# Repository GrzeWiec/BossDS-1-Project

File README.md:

# BossDS-1-Project

My first steps in the world of analog electronics:
- learning the principle of operation of basic electronic components,
- creating the first schematic and PCB in KiCad,
- work based on the famous Boss DS-1 guitar effect,
- getting basic knowledge about the approach to working with an audio signal in electronics.

I created the effect diagram based on the diagram found on the website: https://www.electrosmash.com/boss-ds1-analysis.

All rights to footprints, names, models or symbols belong to their original creators (Boss, SparkFun, M.B.I.)

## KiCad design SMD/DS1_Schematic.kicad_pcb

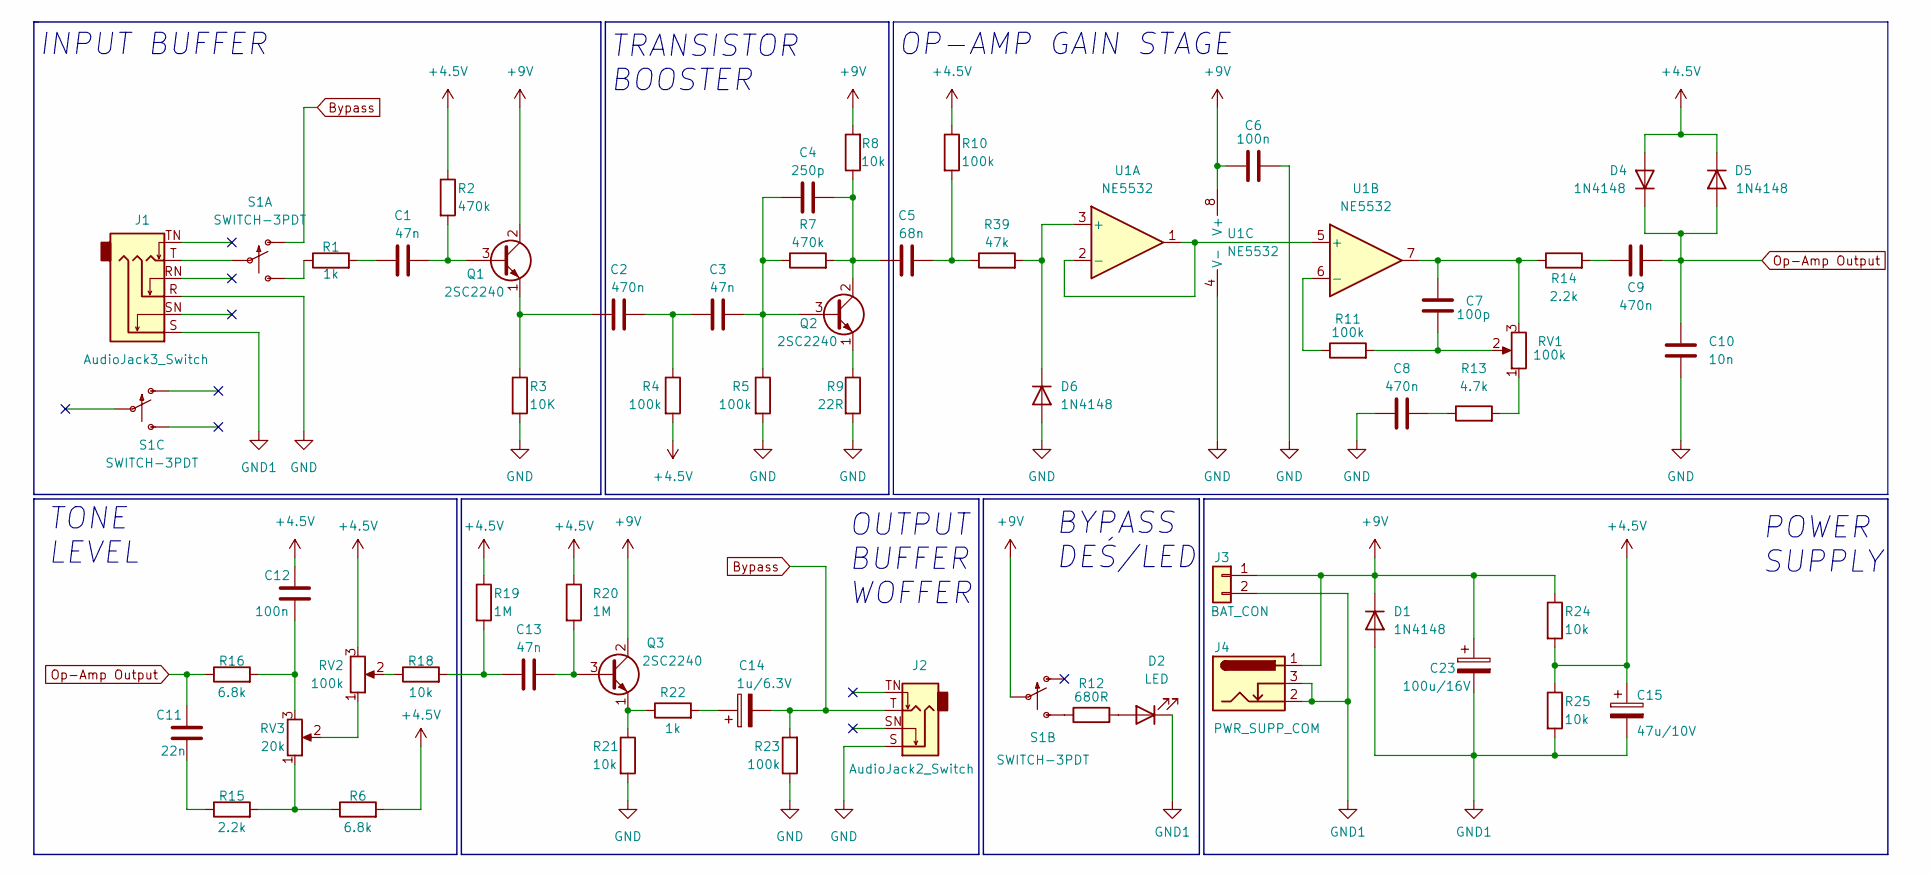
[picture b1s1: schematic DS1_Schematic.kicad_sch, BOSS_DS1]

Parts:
C1, C3, C13: 47n; C_1206_3216Metric_Pad1.33x1.80mm_HandSolder
C2, C8, C9: 470n; C_1206_3216Metric_Pad1.33x1.80mm_HandSolder
C4: 250p; C_1206_3216Metric_Pad1.33x1.80mm_HandSolder
C5: 68n; C_1206_3216Metric_Pad1.33x1.80mm_HandSolder
C6, C12: 100n; C_1206_3216Metric_Pad1.33x1.80mm_HandSolder
C7: 100p; C_1206_3216Metric_Pad1.33x1.80mm_HandSolder
C10: 10n; C_1206_3216Metric_Pad1.33x1.80mm_HandSolder
C11: 22n; C_1206_3216Metric_Pad1.33x1.80mm_HandSolder
C14: 1u/6.3V; C_Elec_4x5.4
C15: 47u/10V; C_1206_3216Metric_Pad1.33x1.80mm_HandSolder
C23: 100u/16V; C_Elec_5x5.8
D1, D4, D5, D6: 1N4148; D_1206_3216Metric_Pad1.42x1.75mm_HandSolder
D2: LED; LED_1206_3216Metric_Pad1.42x1.75mm_HandSolder
J1: AudioJack3_Switch; Jack_6.35mm_Neutrik_NMJ6HFD2_Horizontal
J2: AudioJack2_Switch; Jack_6.35mm_Neutrik_NMJ4HFD2_Horizontal
J3: BAT_CON; PinHeader_1x02_P2.54mm_Vertical
J4: PWR_SUPP_COM; BarrelJack_Wuerth_6941xx301002
Q1, Q2, Q3: 2SC2240; TO-92L_Inline
R1, R22: 1k; R_1206_3216Metric_Pad1.30x1.75mm_HandSolder
R2, R7: 470k; R_1206_3216Metric_Pad1.30x1.75mm_HandSolder
R3: 10K; R_1206_3216Metric_Pad1.30x1.75mm_HandSolder
R4, R5, R10, R11, R23: 100k; R_1206_3216Metric_Pad1.30x1.75mm_HandSolder
R6, R16: 6.8k; R_1206_3216Metric_Pad1.30x1.75mm_HandSolder
R8, R18, R21, R24, R25: 10k; R_1206_3216Metric_Pad1.30x1.75mm_HandSolder
R9: 22R; R_1206_3216Metric_Pad1.30x1.75mm_HandSolder
R12: 680R; R_1206_3216Metric_Pad1.30x1.75mm_HandSolder
R13: 4.7k; R_1206_3216Metric_Pad1.30x1.75mm_HandSolder
R14, R15: 2.2k; R_1206_3216Metric_Pad1.30x1.75mm_HandSolder
R19, R20: 1M; R_1206_3216Metric_Pad1.30x1.75mm_HandSolder
R39: 47k; R_1206_3216Metric_Pad1.30x1.75mm_HandSolder
RV1, RV2: 100k; PinHeader_1x03_P2.54mm_Vertical
RV3: 20k; PinHeader_1x03_P2.54mm_Vertical
S1: SWITCH-3PDT; STOMP-SWITCH-3PDT
U1: NE5532; DIP-8_W7.62mm_LongPads

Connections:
+4.5V: C12.1, C15.1, D4.2 (A), D5.1 (K), R2.1, R4.2, R6.2, R10.1, R19.1, R20.1, R24.2, R25.1, RV2.3
+9V: C6.1, C23.1, D1.1 (K), J3.1, J4.1, Q1.2 (C), Q3.2 (C), R8.2, R24.1, S1.P$5, U1.8 (V+)
Bypass: C14.2, J2.T, R23.2, S1.P$1 (O)
GND: C6.2, C8.1, C10.2, D6.2 (A), J1.R, J2.S, R3.2, R5.2, R9.2, R21.2, R23.1, U1.4 (V-)
GND1: C15.2, C23.2, D1.2 (A), D2.1 (K), J1.S, J3.2, J4.2, J4.3, R25.2
unnamed: C1.1, R1.2
unnamed: C1.2, Q1.3 (B), R2.2
unnamed: C2.1, Q1.1 (E), R3.1
unnamed: C2.2, C3.2, R4.1
unnamed: C3.1, C4.1, Q2.3 (B), R5.1, R7.1
unnamed: C4.2, C5.2, Q2.2 (C), R7.2, R8.1
unnamed: C5.1, R10.2, R39.1
unnamed: C7.1, R14.1, RV1.3, U1.7
unnamed: C7.2, R11.2, RV1.2
unnamed: C8.2, R13.1
unnamed: C9.1, R14.2
unnamed: C11.2, R15.1
unnamed: C12.2, R16.2, RV3.3
unnamed: C13.1, Q3.3 (B), R20.2
unnamed: C13.2, R18.2, R19.2
unnamed: C14.1, R22.2
unnamed: D2.2 (A), R12.2
unnamed: D6.1 (K), R39.2, U1.3 (+)
unnamed: J1.T, S1.P$2
unnamed: Q2.1 (E), R9.1
unnamed: Q3.1 (E), R21.1, R22.1
unnamed: R1.1, S1.P$3 (S)
unnamed: R11.1, U1.6 (-)
unnamed: R12.1, S1.P$6 (S)
unnamed: R13.2, RV1.1
unnamed: R6.1, R15.2, RV3.1
unnamed: R18.1, RV2.2
unnamed: RV2.1, RV3.2
unnamed: U1.1, U1.2 (-), U1.5 (+)
Op-Amp Output: C9.2, C10.1, C11.1, D4.1 (K), D5.2 (A), R16.1

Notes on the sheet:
OUTPUT BUFFER WOFFER
INPUT BUFFER
TRANSISTOR BOOSTER
BYPASS DEŚ/LED
OP-AMP GAIN STAGE
POWER SUPPLY
TONE LEVEL

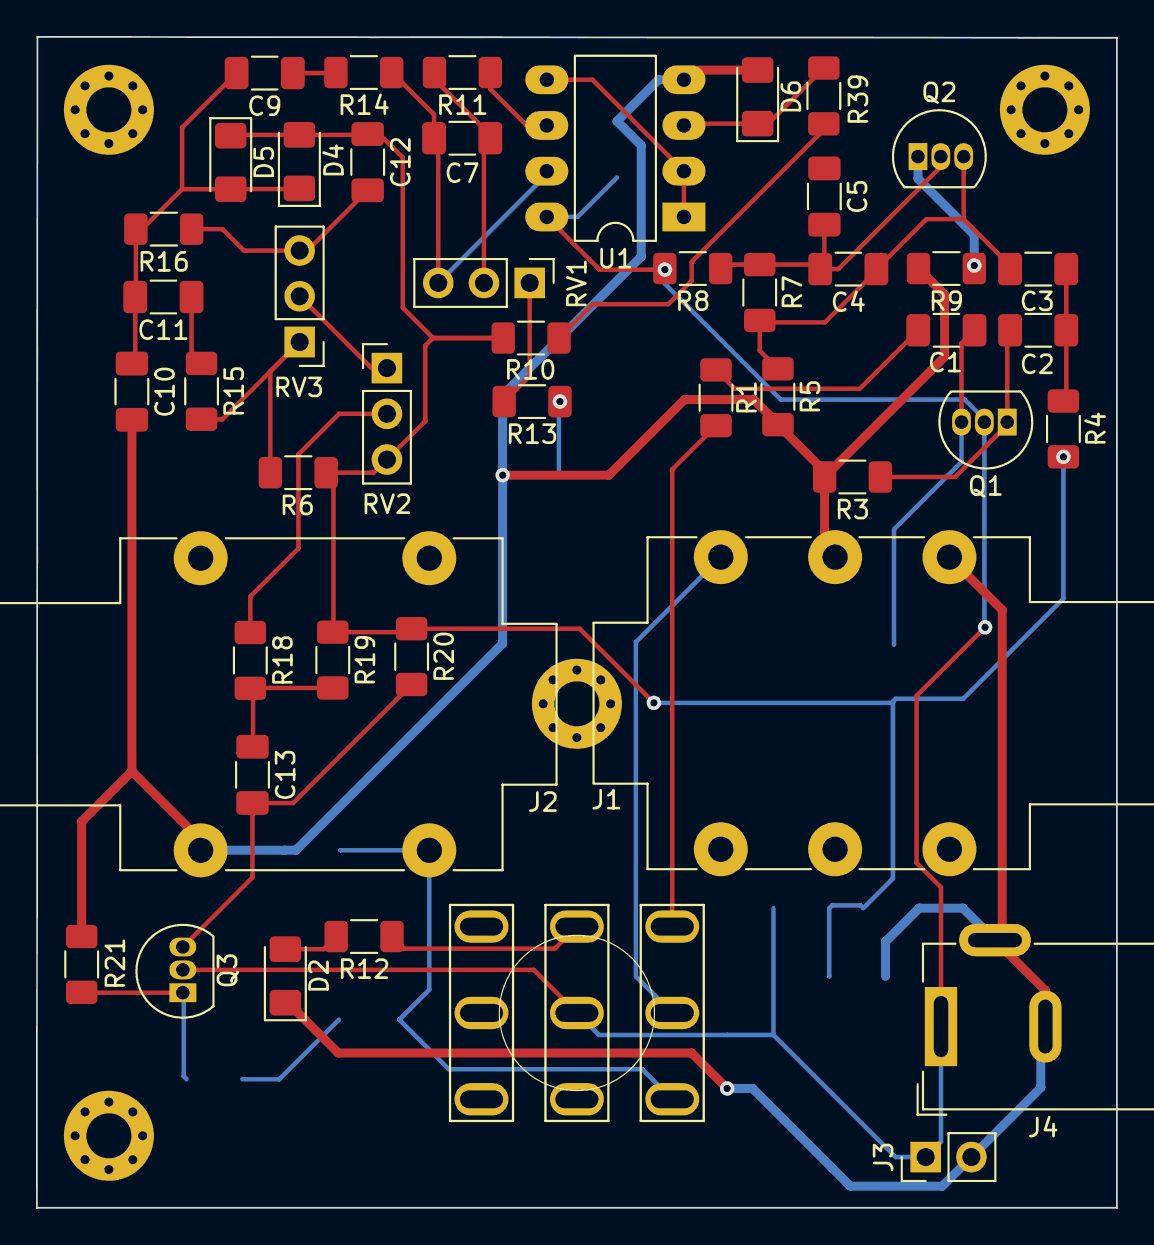
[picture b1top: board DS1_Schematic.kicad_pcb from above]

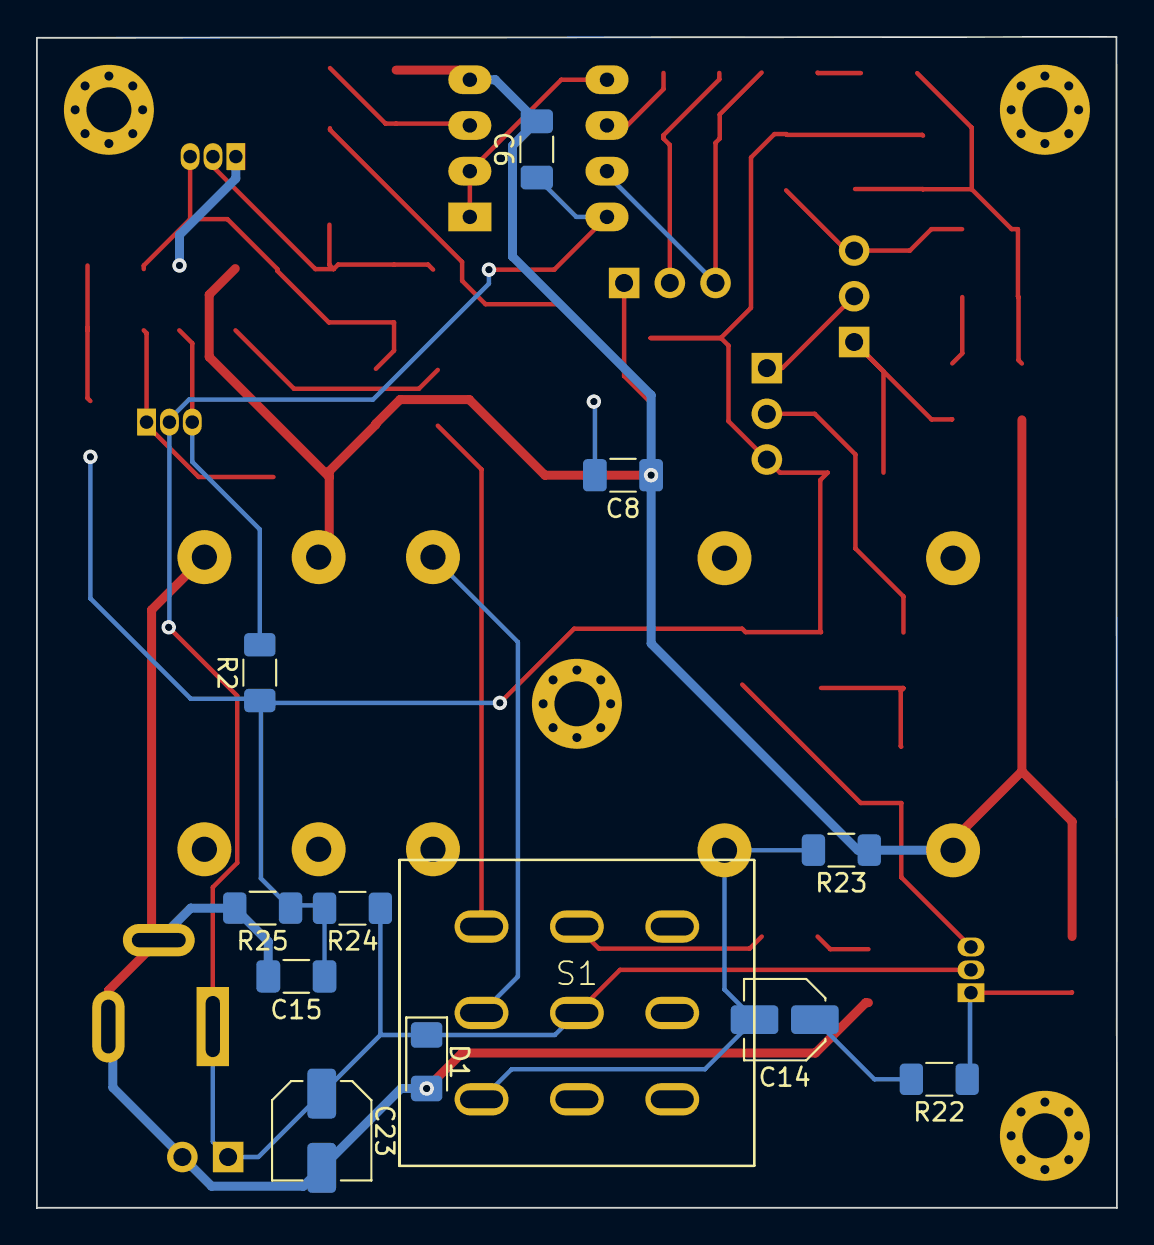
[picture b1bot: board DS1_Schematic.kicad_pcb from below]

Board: 2 copper layers, 60.0 x 65.0 mm, 58 parts (11 on the bottom side), 35 nets.

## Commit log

2023-01-17 inital commit
2023-01-19 new version of THT PSB
2023-01-19 version 2.2.1
2023-01-19 removed empty folder
2023-01-19 removed backups, added .jpg
2023-01-20 updated THT
2023-01-23 SMD initial push
2023-01-23 cleaning up
2023-01-30 new smd model
2023-01-30 removing files
